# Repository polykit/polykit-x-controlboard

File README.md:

# Polykit X8 Controlboard

_THIS IS NOT A FINISHED PRODUCT IN ANY WAY AND STILL UNDER HEAVY DEVELOPMENT - USE AT YOUR OWN RISK!_

This repository contains Kicad schematics and PCB layout of a control board for a polyphonic synthesizer.

There is a video playlist on the design process https://makertube.net/w/p/3N2fRjXwT2SfAUv2VkMy3e

Related repositories:

* Voice Card: https://github.com/polykit/polykit-x-voice-card
* Main Board: https://github.com/polykit/polykit-x-mainboard
* Input Board: _soon_
* Software: _soon_
* Power Supply: https://github.com/polykit/eurorack-psu

## BOM
|Reference|Value         |Footprint                                                      |Comment                               |Qty|
|---------|--------------|---------------------------------------------------------------|--------------------------------------|---|
|C1, C2   |100n          |Capacitor_SMD:C_1206_3216Metric                                |                                      |2  |
|D1-D4    |1N4148WS      |Diode_SMD:D_SOD-323                                            |                                      |4  |
|J1       |MCU_BOARD     |Connector_PinHeader_2.54mm:PinHeader_1x16_P2.54mm_Vertical     |optional, when used as MIDI controller|1  |
|J2       |X8_I2C_POWER  |Connector_IDC:IDC-Header_2x05_P2.54mm_Vertical                 |                                      |1  |
|J3       |X8_EXT_DIGITAL|Connector_IDC:IDC-Header_2x05_P2.54mm_Vertical                 |                                      |1  |
|J4       |DISPLAY       |Connector_PinHeader_2.54mm:PinHeader_1x04_P2.54mm_Vertical     |                                      |1  |
|R1-R34   |10k           |Resistor_SMD:R_1206_3216Metric_Pad1.30x1.75mm_HandSolder       |                                      |34 |
|SW1-SW6  |SW_Push       |Button_Switch_THT:SW_PUSH_6mm_H13mm                            |                                      |6  |
|SW7-SW22 |RotaryEncoder |Rotary_Encoder:RotaryEncoder_Bourns_Vertical_PEC12R-3xxxF-Nxxxx|without switch                        |16 |
|U1, U2   |MCP23017_SO   |Package_SO:SOIC-28W_7.5x17.9mm_P1.27mm                         |                                      |2  |

## References

https://www.ti.com/lit/an/slva704/slva704.pdf

https://github.com/horfee/kicad-packages3D/tree/master/Rotary_Encoder.3dshapes

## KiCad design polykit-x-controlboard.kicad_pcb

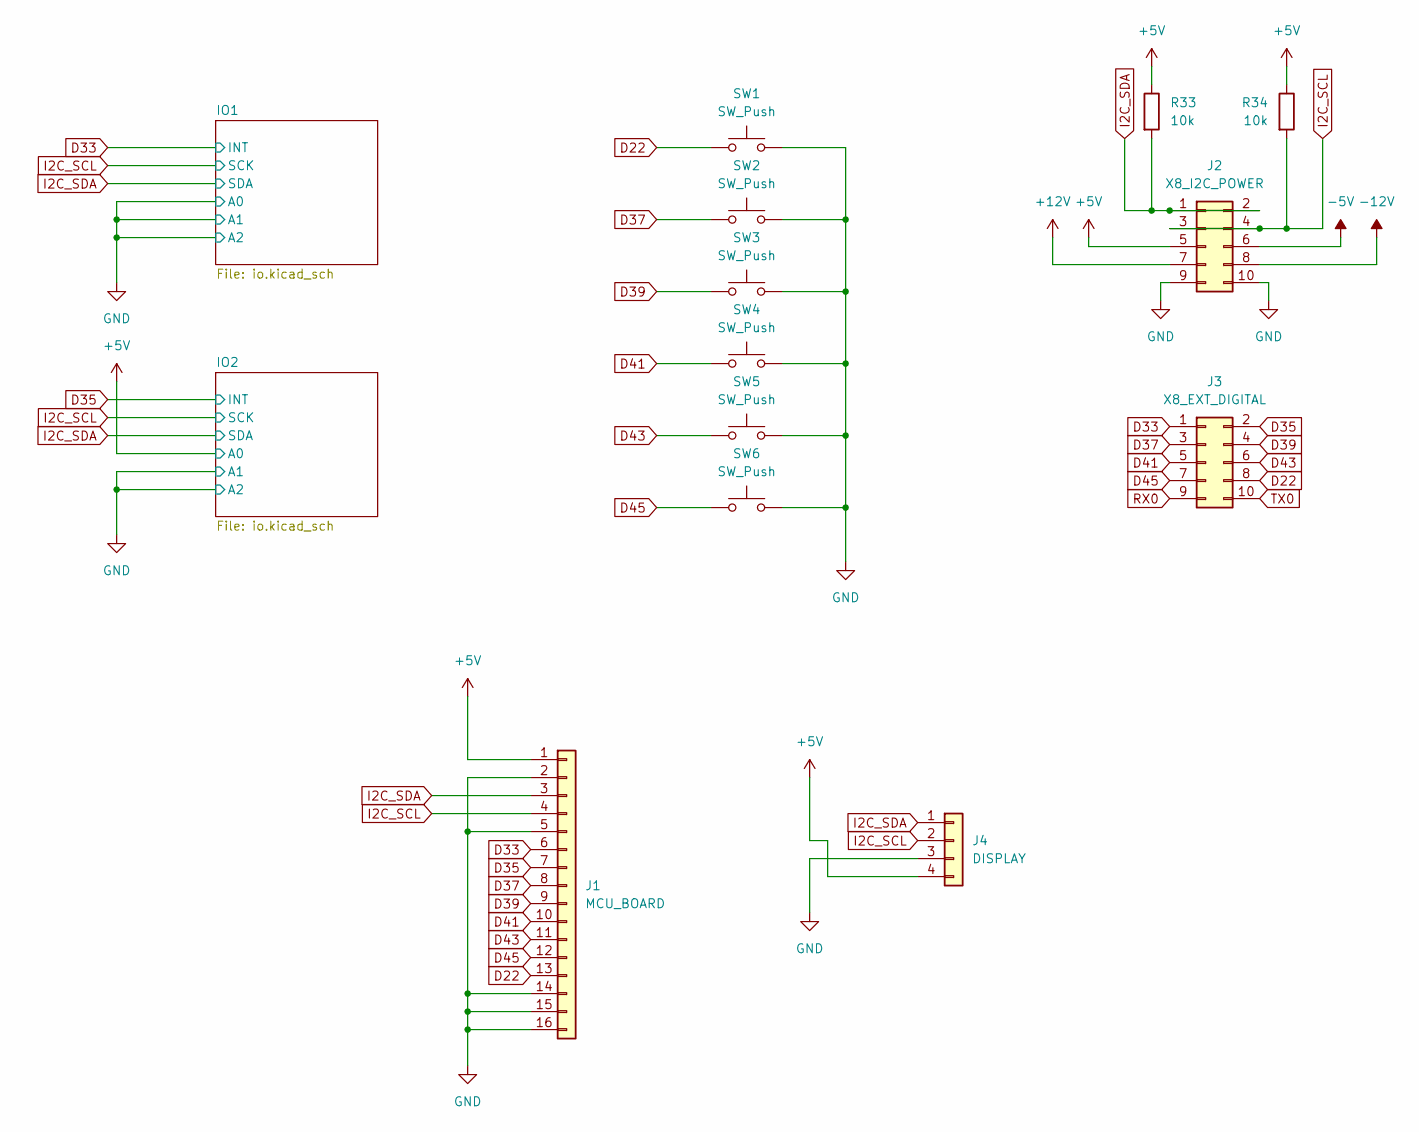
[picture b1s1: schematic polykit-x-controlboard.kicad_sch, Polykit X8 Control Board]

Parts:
J1: MCU_BOARD; PinHeader_1x16_P2.54mm_Vertical
J2: X8_I2C_POWER; IDC-Header_2x05_P2.54mm_Vertical
J3: X8_EXT_DIGITAL; IDC-Header_2x05_P2.54mm_Vertical
J4: DISPLAY; PinHeader_1x04_P2.54mm_Vertical
R33, R34: 10k; R_1206_3216Metric_Pad1.30x1.75mm_HandSolder
SW1, SW2, SW3, SW4, SW5, SW6: SW_Push; SW_PUSH_6mm_H13mm

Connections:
+5V: J1.1, J2.5, J4.4, R33.1, R34.1; also elsewhere on the board
+12V: J2.7
-5V: J2.6
-12V: J2.8
D22: J1.13, J3.8, SW1.1
D33: J1.6, J3.1; also elsewhere on the board
D35: J1.7, J3.2; also elsewhere on the board
D37: J1.8, J3.3, SW2.1
D39: J1.9, J3.4, SW3.1
D41: J1.10, J3.5, SW4.1
D43: J1.11, J3.6, SW5.1
D45: J1.12, J3.7, SW6.1
GND: J1.2, J1.5, J1.14, J1.15, J1.16, J2.9, J2.10, J4.3, SW1.2, SW2.2, SW3.2, SW4.2, SW5.2, SW6.2; also elsewhere on the board
I2C_SCL: J1.4, J2.3, J2.4, J4.2, R34.2; also elsewhere on the board
I2C_SDA: J1.3, J2.1, J2.2, J4.1, R33.2; also elsewhere on the board
RX0: J3.9
TX0: J3.10

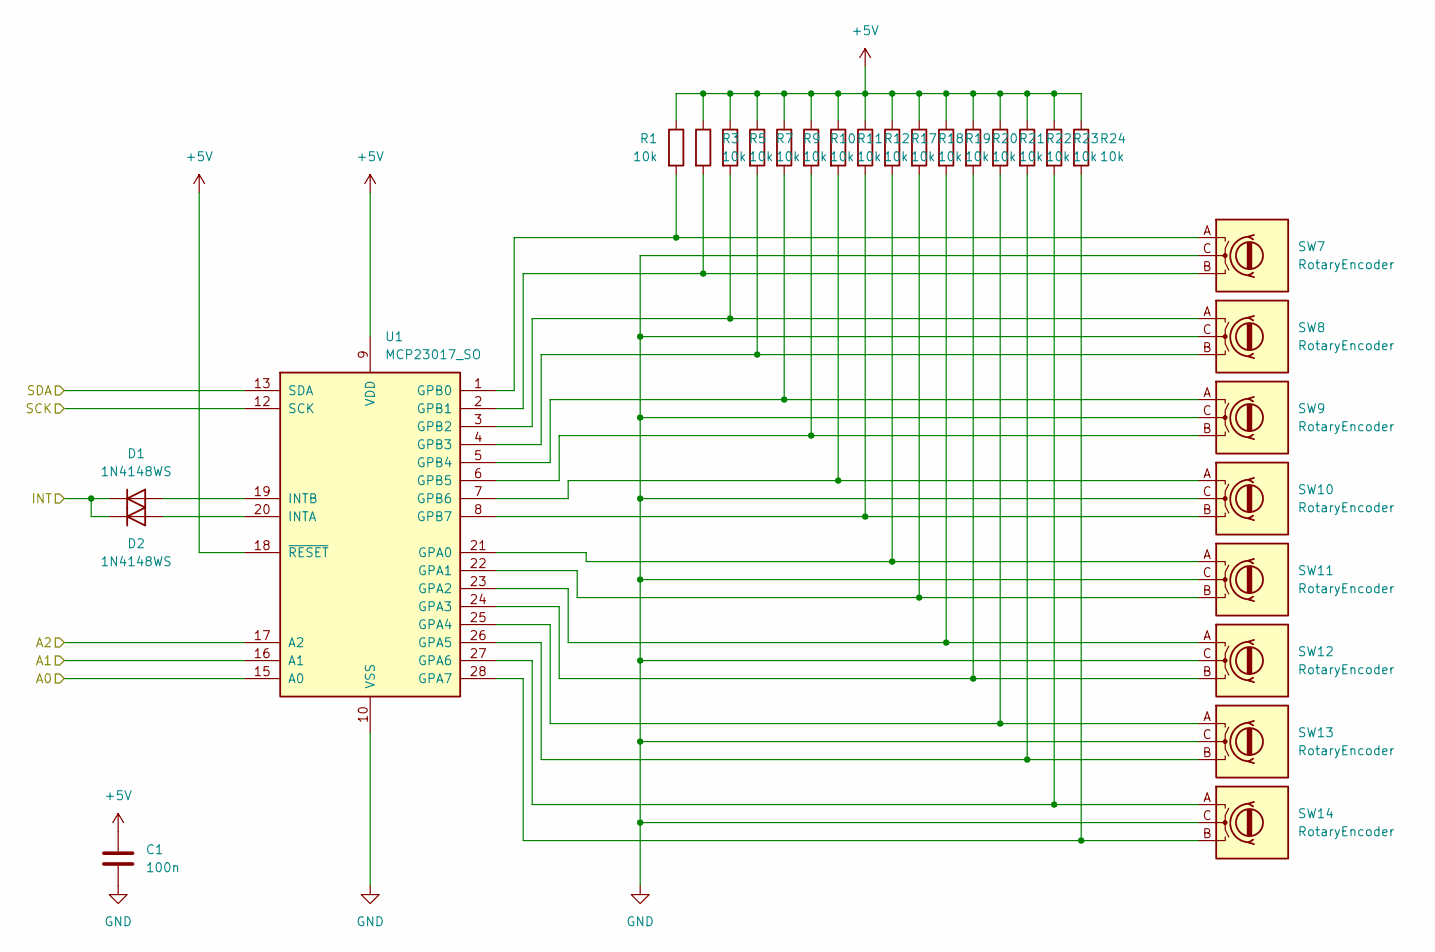
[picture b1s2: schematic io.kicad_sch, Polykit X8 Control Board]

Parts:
C1: 100n; C_1206_3216Metric
D1, D2: 1N4148WS; D_SOD-323
R1, R3, R5, R7, R9, R10, R11, R12, R17, R18, R19, R20, R21, R22, R23, R24: 10k; R_1206_3216Metric_Pad1.30x1.75mm_HandSolder
SW7, SW8, SW9, SW10, SW11, SW12, SW13, SW14: RotaryEncoder; RotaryEncoder_Bourns_Vertical_PEC12R-3xxxF-Nxxxx
U1: MCP23017_SO; SOIC-28W_7.5x17.9mm_P1.27mm

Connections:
+5V: C1.1, R1.1, R3.1, R5.1, R7.1, R9.1, R10.1, R11.1, R12.1, R17.1, R18.1, R19.1, R20.1, R21.1, R22.1, R23.1, R24.1, U1.9 (VDD), U1.18 (~RESET); also elsewhere on the board
D33: D1.1 (K), D2.1 (K); also elsewhere on the board
GND: C1.2, SW7.C, SW8.C, SW9.C, SW10.C, SW11.C, SW12.C, SW13.C, SW14.C, U1.10 (VSS), U1.15 (A0), U1.16 (A1), U1.17 (A2); also elsewhere on the board
I2C_SCL: U1.12 (SCK); also elsewhere on the board
I2C_SDA: U1.13 (SDA); also elsewhere on the board
unnamed: D1.2 (A), U1.19 (INTB)
unnamed: D2.2 (A), U1.20 (INTA)
unnamed: R17.2, SW11.A, U1.21 (GPA0)
unnamed: R18.2, SW11.B, U1.22 (GPA1)
unnamed: R19.2, SW12.A, U1.23 (GPA2)
unnamed: R20.2, SW12.B, U1.24 (GPA3)
unnamed: R21.2, SW13.A, U1.25 (GPA4)
unnamed: R22.2, SW13.B, U1.26 (GPA5)
unnamed: R23.2, SW14.A, U1.27 (GPA6)
unnamed: R24.2, SW14.B, U1.28 (GPA7)
unnamed: R1.2, SW7.A, U1.1 (GPB0)
unnamed: R3.2, SW7.B, U1.2 (GPB1)
unnamed: R5.2, SW8.A, U1.3 (GPB2)
unnamed: R7.2, SW8.B, U1.4 (GPB3)
unnamed: R9.2, SW9.A, U1.5 (GPB4)
unnamed: R10.2, SW9.B, U1.6 (GPB5)
unnamed: R11.2, SW10.A, U1.7 (GPB6)
unnamed: R12.2, SW10.B, U1.8 (GPB7)

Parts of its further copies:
C2: 100n; C_1206_3216Metric
D3, D4: 1N4148WS; D_SOD-323
R2, R4, R6, R8, R13, R14, R15, R16, R25, R26, R27, R28, R29, R30, R31, R32: 10k; R_1206_3216Metric_Pad1.30x1.75mm_HandSolder
SW15, SW16, SW17, SW18, SW19, SW20, SW21, SW22: RotaryEncoder; RotaryEncoder_Bourns_Vertical_PEC12R-3xxxF-Nxxxx
U2: MCP23017_SO; SOIC-28W_7.5x17.9mm_P1.27mm

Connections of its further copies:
+5V: C2.1, R2.1, R4.1, R6.1, R8.1, R13.1, R14.1, R15.1, R16.1, R25.1, R26.1, R27.1, R28.1, R29.1, R30.1, R31.1, R32.1, U2.9 (VDD), U2.15 (A0), U2.18 (~RESET); also elsewhere on the board
D35: D3.1 (K), D4.1 (K); also elsewhere on the board
GND: C2.2, SW15.C, SW16.C, SW17.C, SW18.C, SW19.C, SW20.C, SW21.C, SW22.C, U2.10 (VSS), U2.16 (A1), U2.17 (A2); also elsewhere on the board
I2C_SCL: U2.12 (SCK); also elsewhere on the board
I2C_SDA: U2.13 (SDA); also elsewhere on the board
unnamed: D3.2 (A), U2.19 (INTB)
unnamed: D4.2 (A), U2.20 (INTA)
unnamed: R25.2, SW19.A, U2.21 (GPA0)
unnamed: R26.2, SW19.B, U2.22 (GPA1)
unnamed: R27.2, SW20.A, U2.23 (GPA2)
unnamed: R28.2, SW20.B, U2.24 (GPA3)
unnamed: R29.2, SW21.A, U2.25 (GPA4)
unnamed: R30.2, SW21.B, U2.26 (GPA5)
unnamed: R31.2, SW22.A, U2.27 (GPA6)
unnamed: R32.2, SW22.B, U2.28 (GPA7)
unnamed: R2.2, SW15.A, U2.1 (GPB0)
unnamed: R4.2, SW15.B, U2.2 (GPB1)
unnamed: R6.2, SW16.A, U2.3 (GPB2)
unnamed: R8.2, SW16.B, U2.4 (GPB3)
unnamed: R13.2, SW17.A, U2.5 (GPB4)
unnamed: R14.2, SW17.B, U2.6 (GPB5)
unnamed: R15.2, SW18.A, U2.7 (GPB6)
unnamed: R16.2, SW18.B, U2.8 (GPB7)

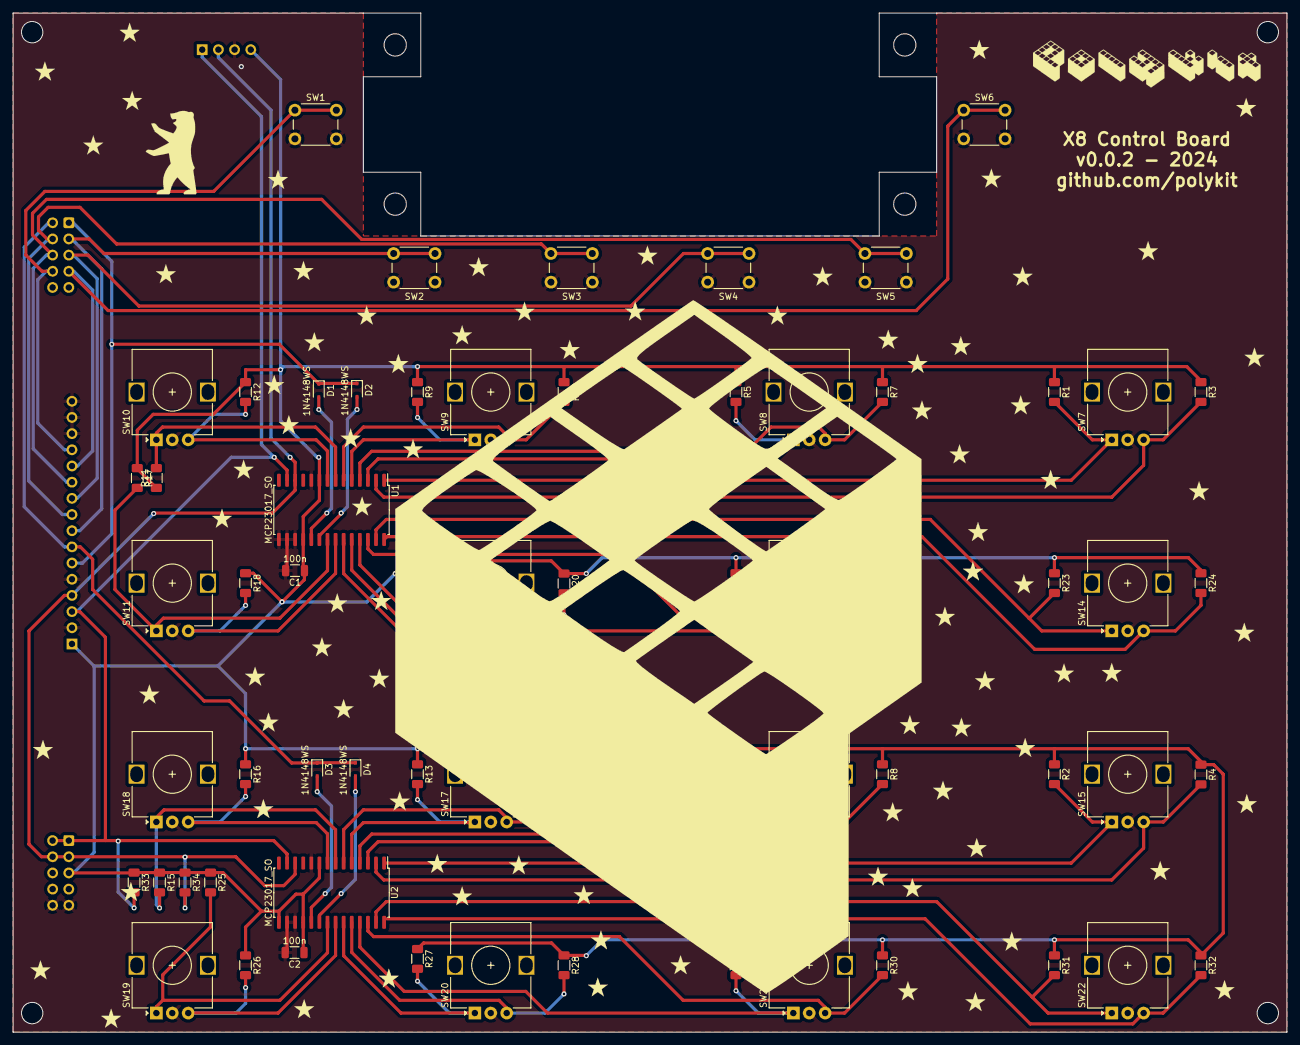
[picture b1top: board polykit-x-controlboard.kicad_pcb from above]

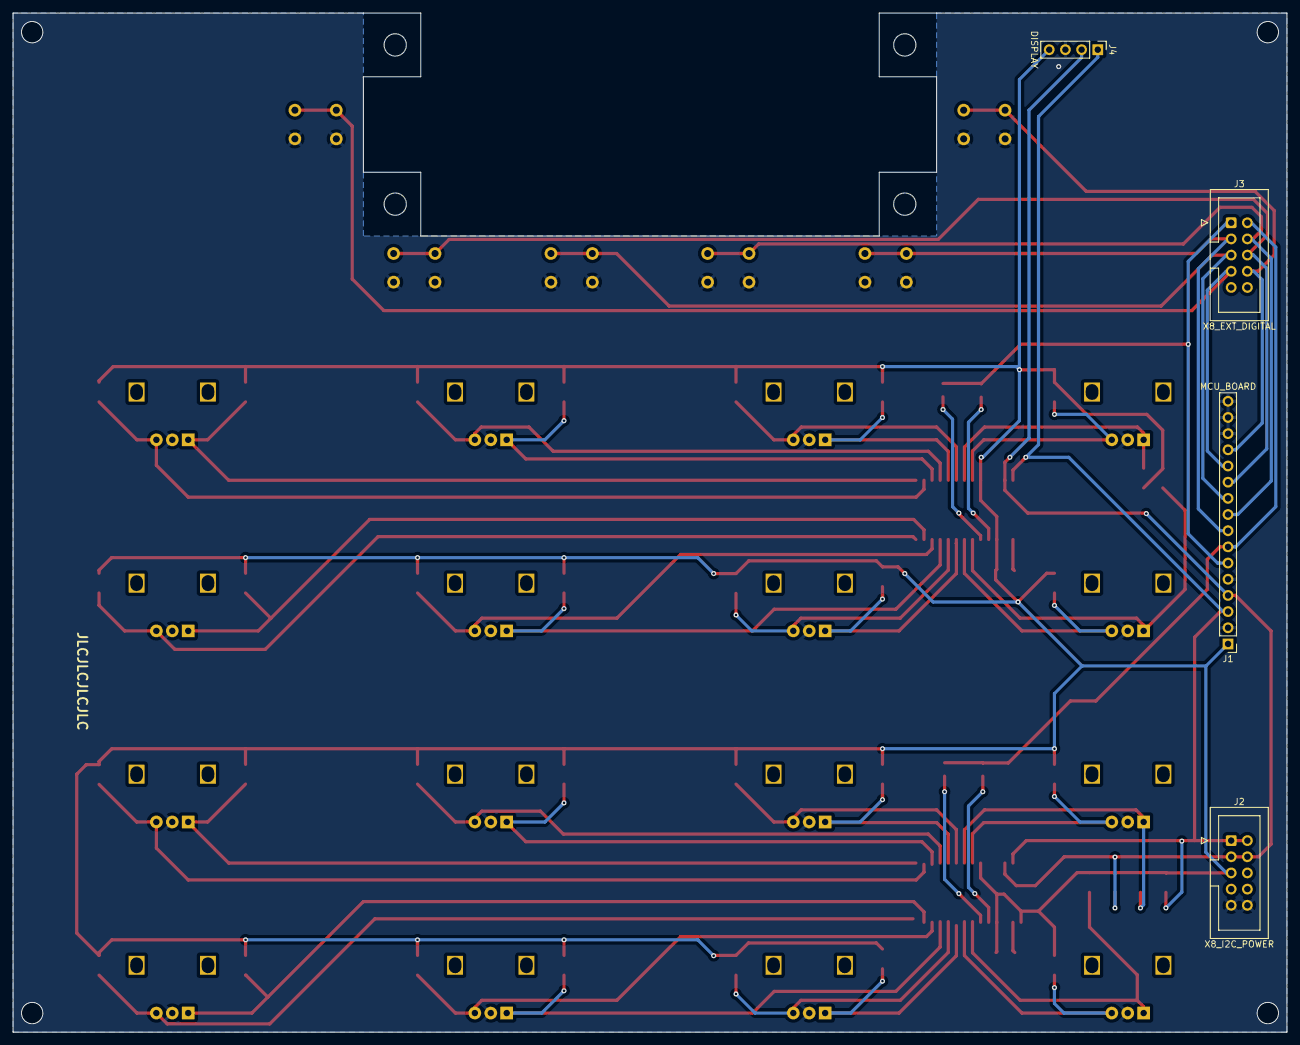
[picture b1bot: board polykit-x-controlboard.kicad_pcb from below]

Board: 2 copper layers, 200.0 x 160.0 mm, 68 parts (4 on the bottom side), 48 nets.

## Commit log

2024-02-07 Initial import
2024-02-07 Update readme, rendering
2024-02-07 Add bom
2024-02-07 Add video to readme
2024-02-07 Add playlist to readme
2025-05-09 Add license
